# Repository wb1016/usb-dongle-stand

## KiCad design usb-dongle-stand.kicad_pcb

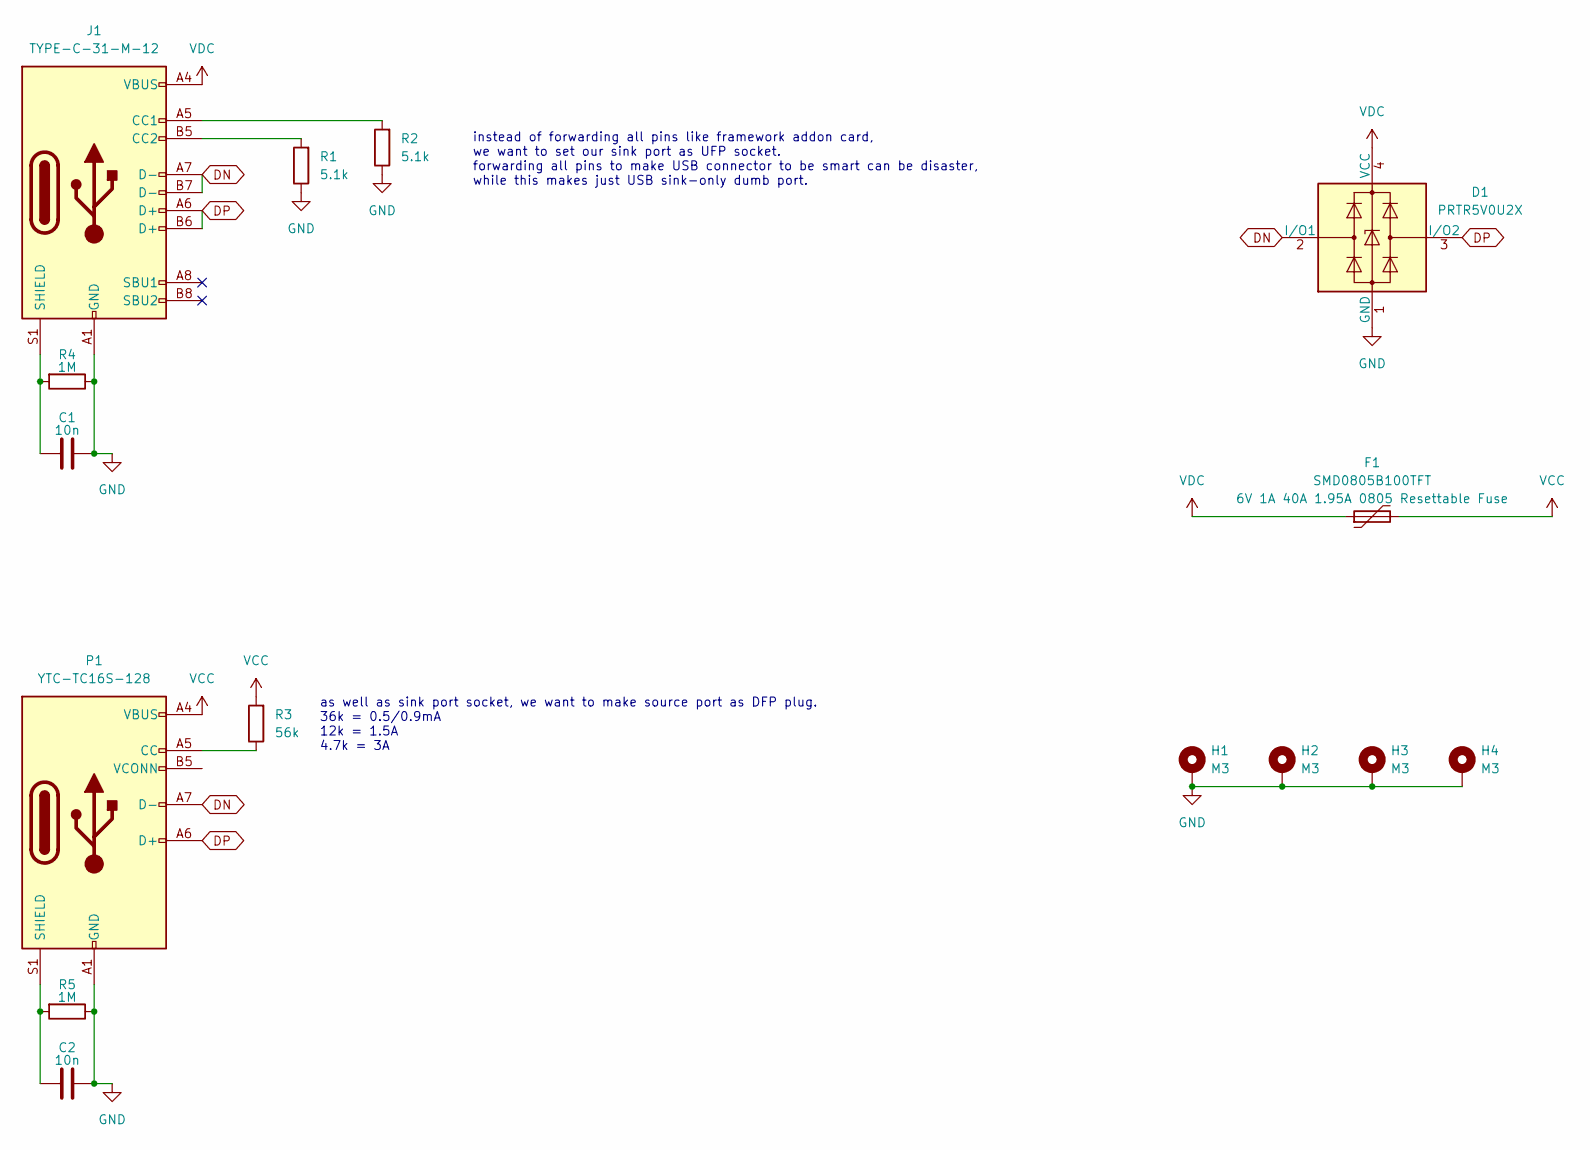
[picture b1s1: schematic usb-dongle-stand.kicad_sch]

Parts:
C1, C2: 10n; C_0603_1608Metric
D1: PRTR5V0U2X; SOT-143
F1: SMD0805B100TFT; Fuse_0805_2012Metric
H1, H2, H3, H4: M3; MountingHole_3.2mm_M3_ISO14580_Pad
J1: TYPE-C-31-M-12; USB_C_Receptacle_HRO_TYPE-C-31-M-12
P1: YTC-TC16S-128; TYPE-C-SMD_YTC-TC16S-128
R1, R2: 5.1k; R_0603_1608Metric
R3: 56k; R_0603_1608Metric
R4, R5: 1M; R_0603_1608Metric

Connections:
DN: D1.2 (I/O1), J1.A7 (D-), J1.B7 (D-), P1.A7 (D-)
DP: D1.3 (I/O2), J1.A6 (D+), J1.B6 (D+), P1.A6 (D+)
GND: C1.2, C2.2, D1.1 (GND), H1.1, H2.1, H3.1, H4.1, J1.A1 (GND), J1.A12 (GND), J1.B1 (GND), J1.B12 (GND), P1.A1 (GND), P1.A12 (GND), P1.B1 (GND), P1.B12 (GND), R1.1, R2.1, R4.1, R5.1
unnamed: J1.A5 (CC1), R2.2
unnamed: J1.B5 (CC2), R1.2
unnamed: C1.1, J1.S1 (SHIELD), R4.2
unnamed: P1.A5 (CC), R3.1
unnamed: C2.1, P1.S1 (SHIELD), R5.2
VCC: F1.2, P1.A4 (VBUS), P1.A9 (VBUS), P1.B4 (VBUS), P1.B9 (VBUS), R3.2
VDC: D1.4 (VCC), F1.1, J1.A4 (VBUS), J1.A9 (VBUS), J1.B4 (VBUS), J1.B9 (VBUS)

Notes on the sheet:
instead of forwarding all pins like framework addon card, we want to set our sink port as UFP socket. forwarding all pins to make USB connector to be smart can be disaster, while this makes just USB sink-only dumb port.
as well as sink port socket, we want to make source port as DFP plug. 36k = 0.5/0.9mA 12k = 1.5A 4.7k = 3A

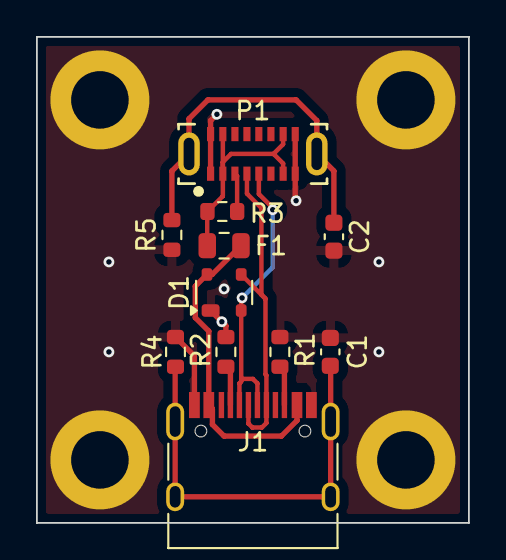
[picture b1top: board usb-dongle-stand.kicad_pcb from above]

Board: 2 copper layers, 24.0 x 27.0 mm, 15 parts (0 on the bottom side), 10 nets.

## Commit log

2025-08-03 done sch, pcb, 3d
2025-08-03 correct DFP CC resistor
